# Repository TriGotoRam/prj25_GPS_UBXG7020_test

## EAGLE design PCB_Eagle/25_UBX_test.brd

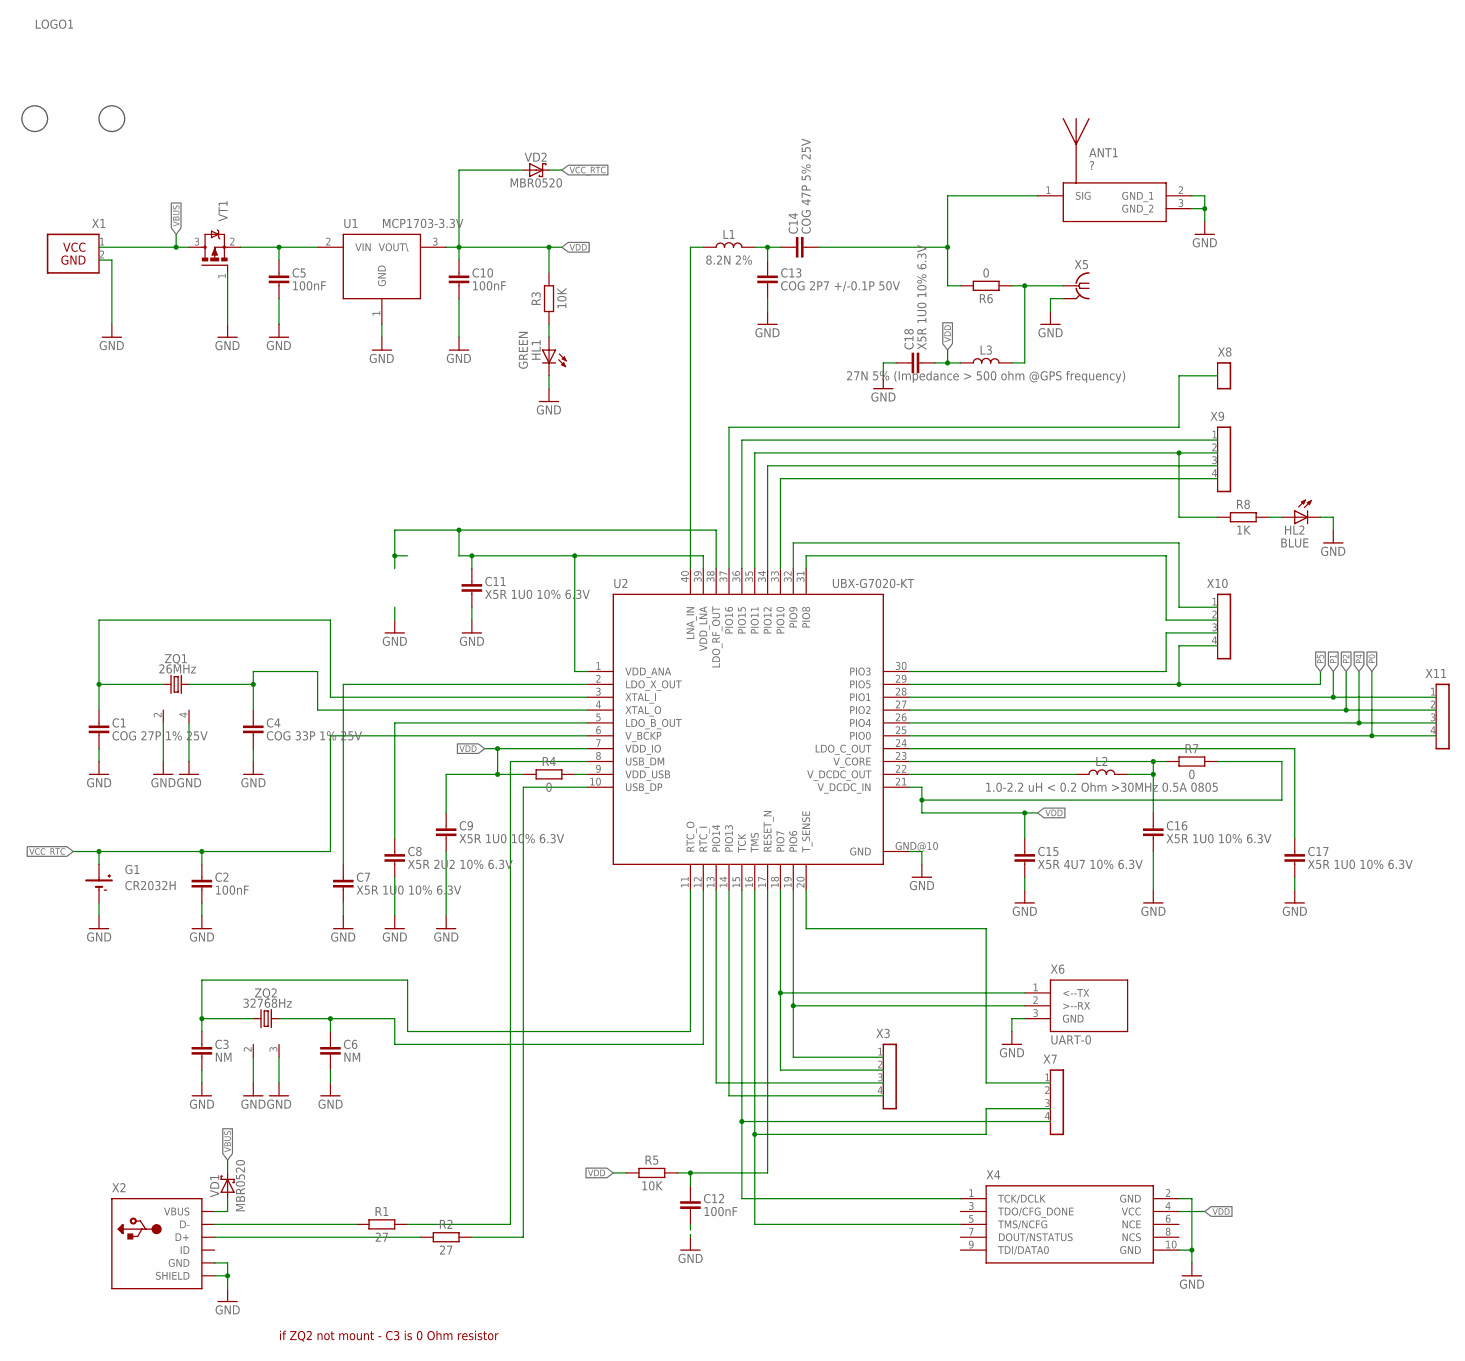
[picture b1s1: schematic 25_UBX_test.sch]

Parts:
ANT1: ?; ANTENNA-GPS-AMAN1003030ST01
C1: COG 27P 1% 25V; C0603
C2, C12: 100nF; C0603
C3, C6: NM; C0402
C4: COG 33P 1% 25V; C0603
C5: 100nF; C0805
C7, C9, C11, C16, C17, C18: X5R 1U0 10% 6.3V; C0603
C8: X5R 2U2 10% 6.3V; C0603
C10: 100nF; C1206
C13: COG 2P7 +/-0.1P 50V; C0603
C14: COG 47P 5% 25V; C0603
C15: X5R 4U7 10% 6.3V; C0603
FIDUCIAL1, FIDUCIAL2: FIDUCIAL-1MM; FIDUCIAL_1MM
G1: CR2032H; SN2032
HL1: GREEN; CHIPLED_0805
HL2: BLUE; CHIPLED_0805
L1: 8.2N 2%; L0603-1
L2: 1.0-2.2 uH < 0.2 Ohm >30MHz 0.5A 0805; L0805
L3: 27N 5% (Impedance > 500 ohm @GPS frequency); L0603-1
LOGO1: LOGO6; LOGO_OMEGA
R1, R2: 27; R0603
R3, R5: 10K; R0603
R4: 0; R0805
R6, R7: 0; R0603
R8: 1K; R0603
U1: MCP1703-3.3V; SOT89
U2: UBX-G7020-KT; QFN40-5X5
VD1, VD2: MBR0520; SOD123
VT1: FET_P-SOT23; SOT23-3-1
X1: CON-2P-1; PLS-2.54-2
X2: USB-5S-MINI; USB-MINIB-1
X3, X7, X9, X10, X11: CON-4PPLS2-4; PLS2-4
X4: JTAG-ALTERA-5X2PINHEAD; ML10_NEW
X5: U.FL-2; U.FL.-4PIN
X6: UART-0; PLS-2.54-3
X8: CON-1PPLS2-1; PLS2-1
ZQ1: 26MHz; CRYSTAL-SMD-3225
ZQ2: 32768Hz; SJK-7M

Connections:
ANT: ANT1.1 (SIG), C14.2, R6.1
D_N: R1.1, U2.8 (USB_DM)
D_P: R2.1, U2.10 (USB_DP)
GND: ANT1.2 (GND_1), ANT1.3 (GND_2), C1.2, C2.2, C3.2, C4.2, C5.2, C6.2, C7.2, C8.2, C9.2, C10.2, C11.2, C12.2, C13.2, C15.2, C16.2, C17.2, C18.1, G1.-BATT (-), HL1.C, HL2.C, U1.1 (GND), U2.GND@10 (GND), VT1.1 (G), X1.2, X2.GND, X2.SHIELD@1 (SHIELD), X2.SHIELD@2 (SHIELD), X2.SHIELD@3 (SHIELD), X2.SHIELD@4 (SHIELD), X4.2 (GND), X4.10 (GND), X5.S@1 (GND), X5.S@2 (GND), X5.S@3 (GND), X6.3 (GND), ZQ1.2 (S), ZQ1.4 (S), ZQ2.2 (S), ZQ2.3 (S)
unnamed: VD1.A, X2.VBUS
unnamed: L3.1 (%1), R6.2, X5.1
unnamed: HL1.A, R3.1
unnamed: C8.1, U2.5 (LDO_B_OUT)
unnamed: C17.1, U2.24 (LDO_C_OUT)
unnamed: L1.1 (%1), U2.40 (LNA_IN)
unnamed: C13.1, C14.1, L1.2 (%2)
unnamed: R1.2, X2.D-
unnamed: R2.2, X2.D+
unnamed: C7.1, U2.2 (LDO_X_OUT)
unnamed: C11.1, U2.1 (VDD_ANA), U2.38 (LDO_RF_OUT), U2.39 (VDD_LNA)
unnamed: C5.1, U1.2 (VIN), VT1.2 (S)
unnamed: HL2.A, R8.2
unnamed: R4.1, U2.9 (VDD_USB)
unnamed: L2.1 (%1), U2.22 (V_DCDC_OUT)
unnamed: C16.1, L2.2 (%2), R7.1, U2.23 (V_CORE)
P0: U2.25 (PIO0), X11.4
P1: U2.28 (PIO1), X11.1
P2: U2.27 (PIO2), X11.2
P3: U2.30 (PIO3), X10.3
P4: U2.26 (PIO4), X11.3
P5: U2.29 (PIO5), X10.4
P6: U2.19 (PIO6), X3.1, X6.2 (>--RX)
P7: U2.18 (PIO7), X3.2, X6.1 (<--TX)
P8: U2.31 (PIO8), X10.2
P9: U2.32 (PIO9), X10.1
P10: U2.33 (PIO10), X9.4
P11: R8.1, U2.35 (PIO11), X9.2
P12: U2.34 (PIO12), X9.3
P13: U2.14 (PIO13), X3.4
P14: U2.13 (PIO14), X3.3
P15: U2.36 (PIO15), X9.1
P16: U2.37 (PIO16), X8.1
RES: C12.1, R5.2, U2.17 (RESET_N)
RTCI: C6.1, U2.12 (RTC_I), ZQ2.4 (2)
RTCO: C3.1, U2.11 (RTC_O), ZQ2.1
TCK: U2.15 (TCK), X4.1 (TCK/DCLK), X7.4
TMS: U2.16 (TMS), X4.5 (TMS/NCFG), X7.3
T_SENSE: U2.20 (T_SENSE), X7.1
VBUS: VD1.C, VT1.3 (D), X1.1
VCC_RTC: C2.1, G1.+BATT (+), U2.6 (V_BCKP), VD2.C
VDD: C9.1, C10.1, C15.1, C18.2, L3.2 (%2), R3.2, R4.2, R5.1, R7.2, U1.3 (VOUT\), U2.7 (VDD_IO), U2.21 (V_DCDC_IN), VD2.A, X4.4 (VCC)
XTALI: C1.1, U2.3 (XTAL_I), ZQ1.1
XTALO: C4.1, U2.4 (XTAL_O), ZQ1.3 (2)

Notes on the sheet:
GND
VCC
if ZQ2 not mount - C3 is 0 Ohm resistor

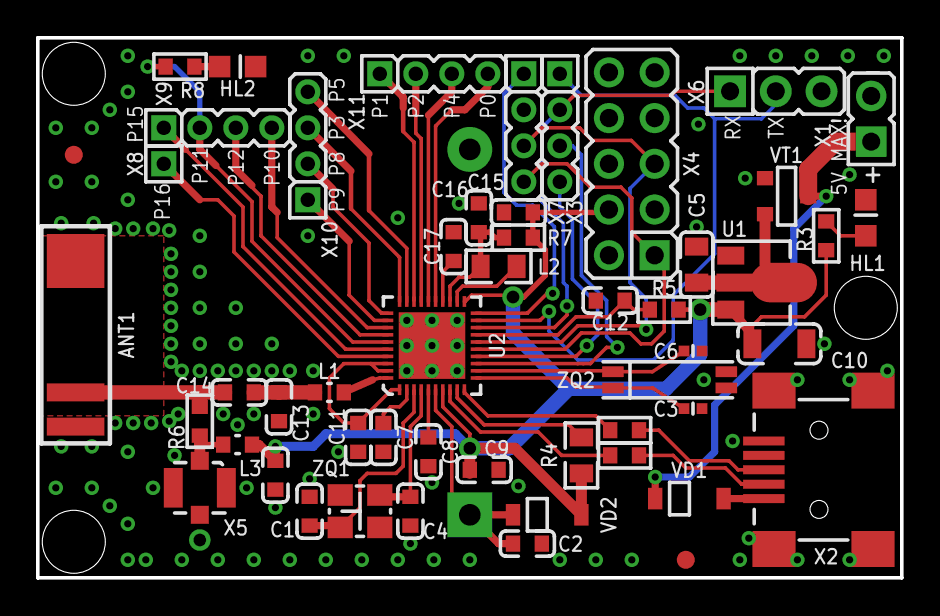
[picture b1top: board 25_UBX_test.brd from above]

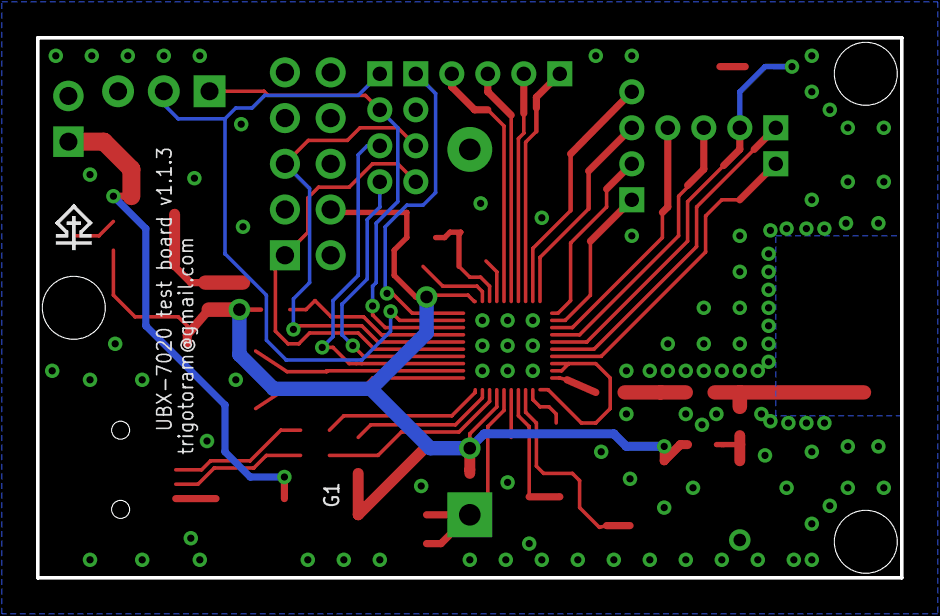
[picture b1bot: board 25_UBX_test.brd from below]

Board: 2 copper layers, 48.0 x 30.0 mm, 54 parts (2 on the bottom side), 48 nets.

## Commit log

2018-07-25 Add README.md
2018-07-25 add pdfs
